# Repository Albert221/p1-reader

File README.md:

# P1 Reader

A simple device connecting a [Seeed ESP32-C3](https://wiki.seeedstudio.com/XIAO_ESP32C3_Getting_Started/) to a P1 port of the electricity meter. Based on ESPHome.

> [!NOTE]
> This project is dedicated to working with Polish STOEN operator, using GAMA 350 meter.

## KiCAD

In `kicad/MJ3235-66-0` directory you should put a 3D model of the RJ12 connector that you can get from [here](https://www.tme.eu/pl/details/mj3235-66-0/zlacza-rj/gct/). I'm not sharing it as its license doesn't allow model file redistribution.

In PCB, there is 1K pull-up resistor between Data and 3V3 missing.

## Components

- [RJ12 connector](https://www.tme.eu/pl/details/mj3235-66-0/zlacza-rj/gct/)
- Electrolytic capacitors 100uF, 10uF, 1uF
- Ceramic capacitor 100nF
- Resistors 56Ω, 100Ω, 200Ω, 1kΩ
- Amber LED 3mm
- Optocoupler 4N35
- 2x 1x7 header socket (for connecting to ESP, chip facing down, USB to the edge of PCB)

## Sources

- https://forum.arturhome.pl/t/elgama-gama-350-i-port-p1/13722/21
- https://esphome.io/components/sensor/dsmr/
- https://www.netbeheernederland.nl/sites/default/files/2024-02/dsmr_5.0.2_p1_companion_standard.pdf ([Web Archive](https://web.archive.org/web/20260104071119/https://www.netbeheernederland.nl/sites/default/files/2024-02/dsmr_5.0.2_p1_companion_standard.pdf))

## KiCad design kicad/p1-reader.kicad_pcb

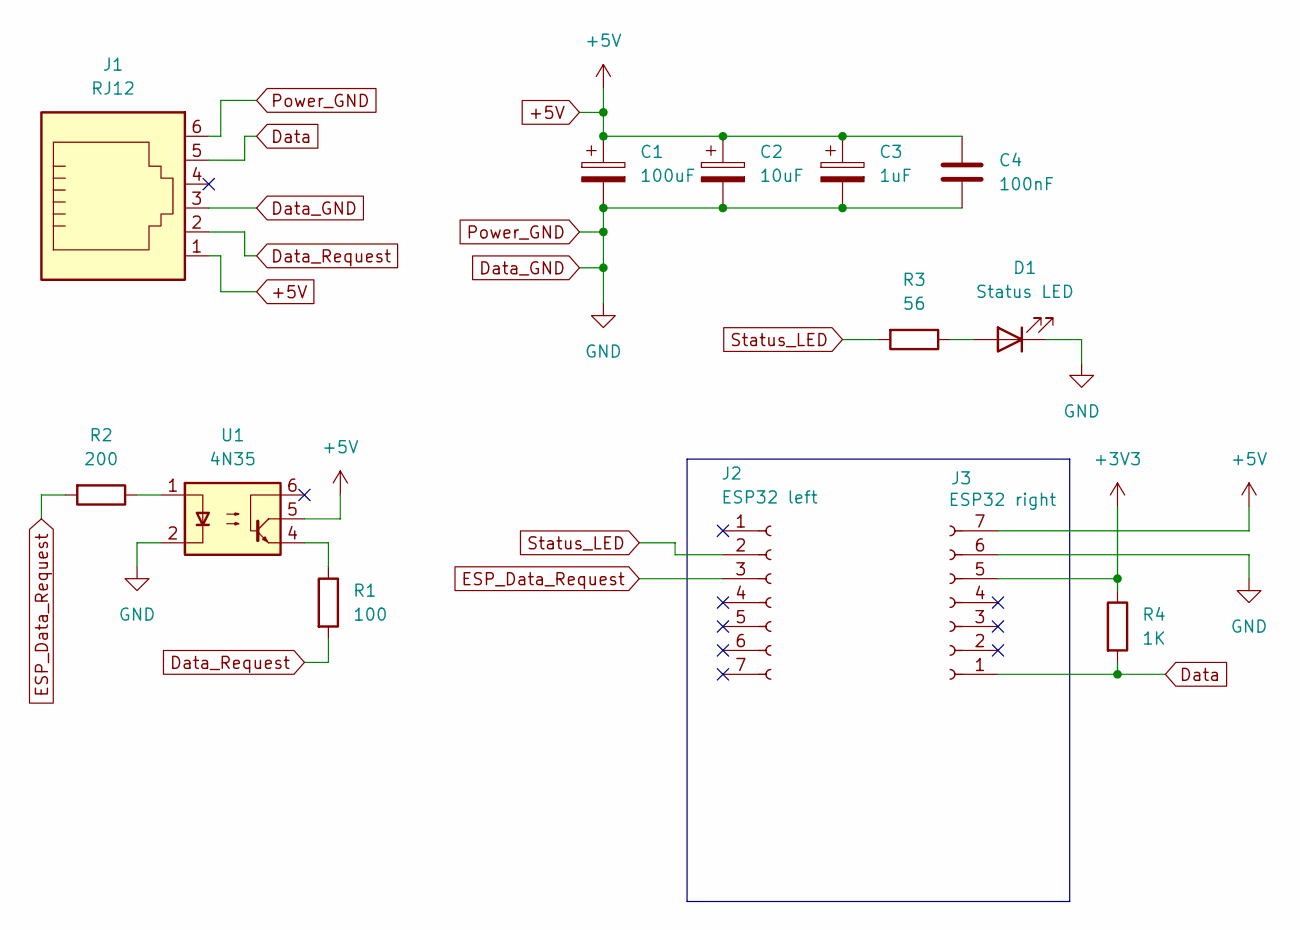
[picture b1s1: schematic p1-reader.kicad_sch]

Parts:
C1: 100uF; CP_Radial_D8.0mm_P3.50mm
C2: 10uF; CP_Radial_D5.0mm_P2.00mm
C3: 1uF; CP_Radial_D5.0mm_P2.50mm
C4: 100nF; C_Disc_D3.0mm_W1.6mm_P2.50mm
D1: Status LED; LED_D3.0mm
J1: RJ12; MJ3235660
J2: ESP32 left; PinSocket_1x07_P2.54mm_Vertical
J3: ESP32 right; PinSocket_1x07_P2.54mm_Vertical
R1: 100; R_Axial_DIN0207_L6.3mm_D2.5mm_P10.16mm_Horizontal
R2: 200; R_Axial_DIN0207_L6.3mm_D2.5mm_P10.16mm_Horizontal
R3: 56; R_Axial_DIN0207_L6.3mm_D2.5mm_P10.16mm_Horizontal
R4: 1K
U1: 4N35; DIP-6_W7.62mm

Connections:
+3V3: J3.5, R4.1
+5V: C1.1, C2.1, C3.1, C4.1, J1.1, J3.7, U1.5
Data: J1.5, J3.1, R4.2
Data_GND: C1.2, C2.2, C3.2, C4.2, D1.1 (K), J1.3, J1.6, J3.6, U1.2
Data_Request: J1.2, R1.2
ESP_Data_Request: J2.3, R2.2
unnamed: D1.2 (A), R3.1
unnamed: R1.1, U1.4
unnamed: R2.1, U1.1
Status_LED: J2.2, R3.2

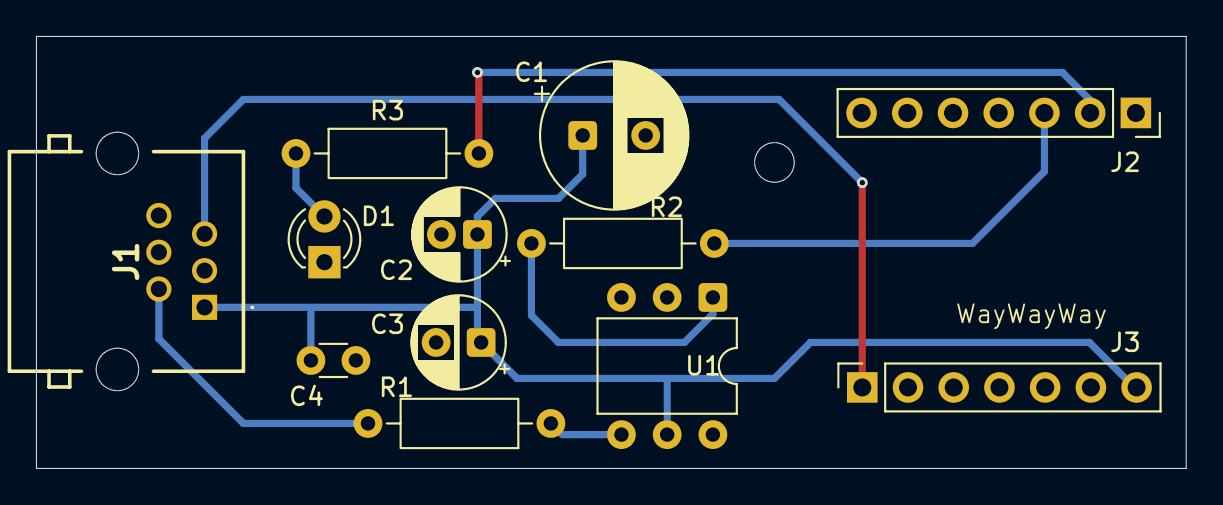
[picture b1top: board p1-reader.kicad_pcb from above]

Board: 2 copper layers, 63.9 x 24.0 mm, 12 parts (0 on the bottom side), 9 nets.

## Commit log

2026-01-06 Add status LED
2026-01-10 Change ESP32 framework type to Arduino
2026-04-02 Update for Stoen
